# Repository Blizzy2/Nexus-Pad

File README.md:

This is Nexus Pad its a simple macro pad with 6 kays and a cool space design.

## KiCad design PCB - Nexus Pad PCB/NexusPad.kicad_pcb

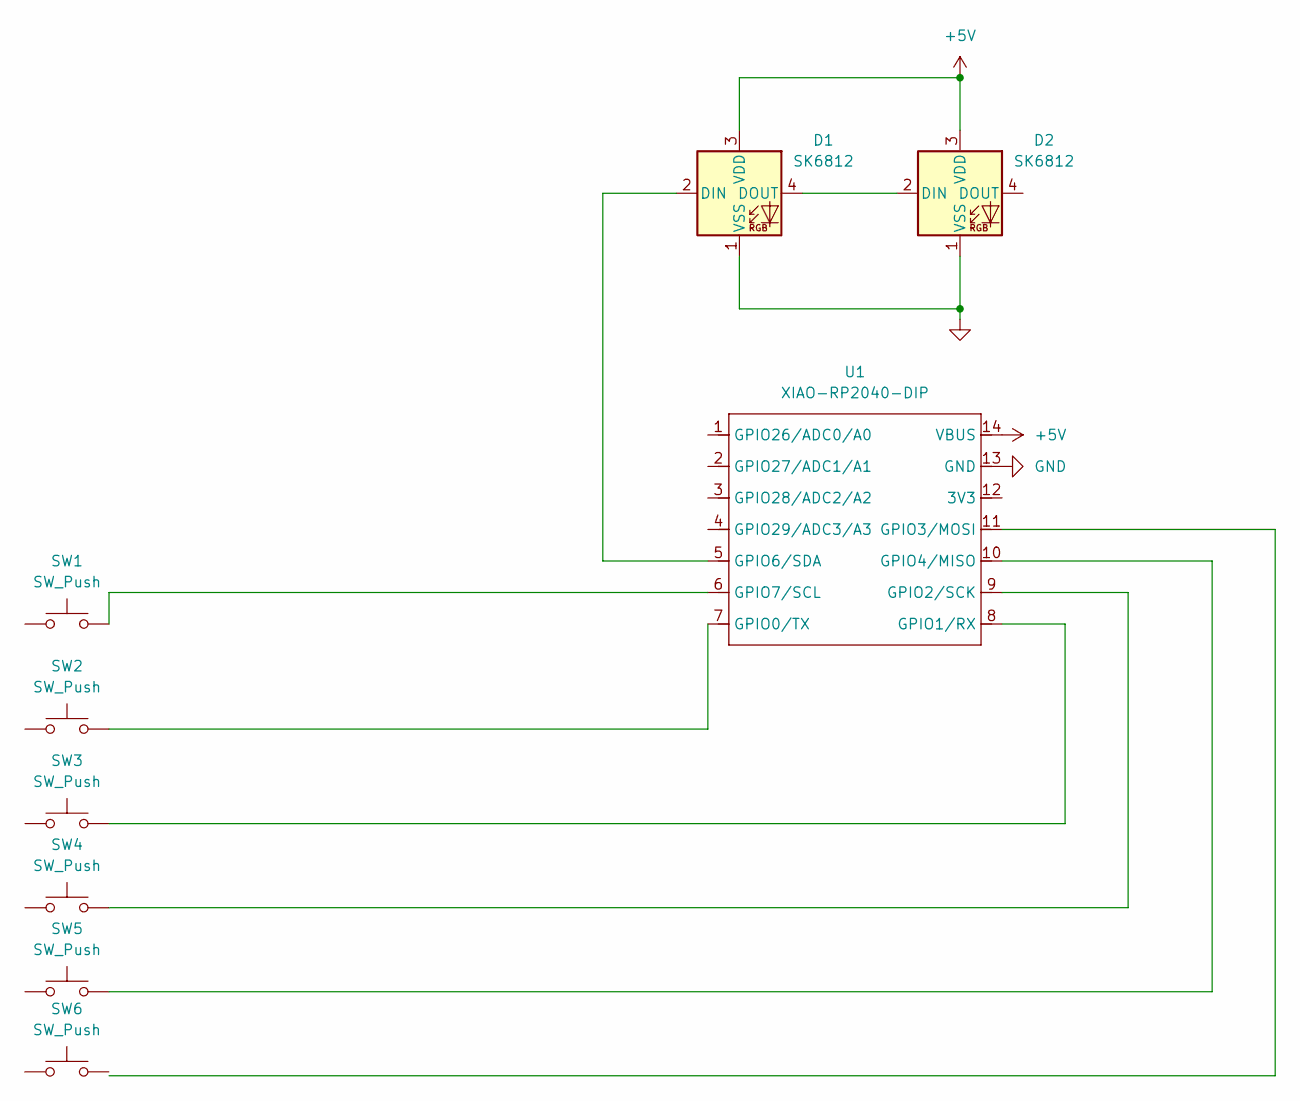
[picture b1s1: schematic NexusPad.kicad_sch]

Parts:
D1, D2: SK6812; LED_SK6812_PLCC4_5.0x5.0mm_P3.2mm
SW1, SW2, SW3, SW4, SW5, SW6: SW_Push; SW_Cherry_MX_1.00u_PCB
U1: XIAO-RP2040-DIP

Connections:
+5V: D1.3 (VDD), D2.3 (VDD), U1.14 (VBUS)
GND: D1.1 (VSS), D2.1 (VSS), U1.13 (GND)
unnamed: D1.2 (DIN), U1.5 (GPIO6/SDA)
unnamed: D1.4 (DOUT), D2.2 (DIN)
unnamed: SW2.2, U1.7 (GPIO0/TX)
unnamed: SW3.2, U1.8 (GPIO1/RX)
unnamed: SW4.2, U1.9 (GPIO2/SCK)
unnamed: SW5.2, U1.10 (GPIO4/MISO)
unnamed: SW1.2, U1.6 (GPIO7/SCL)

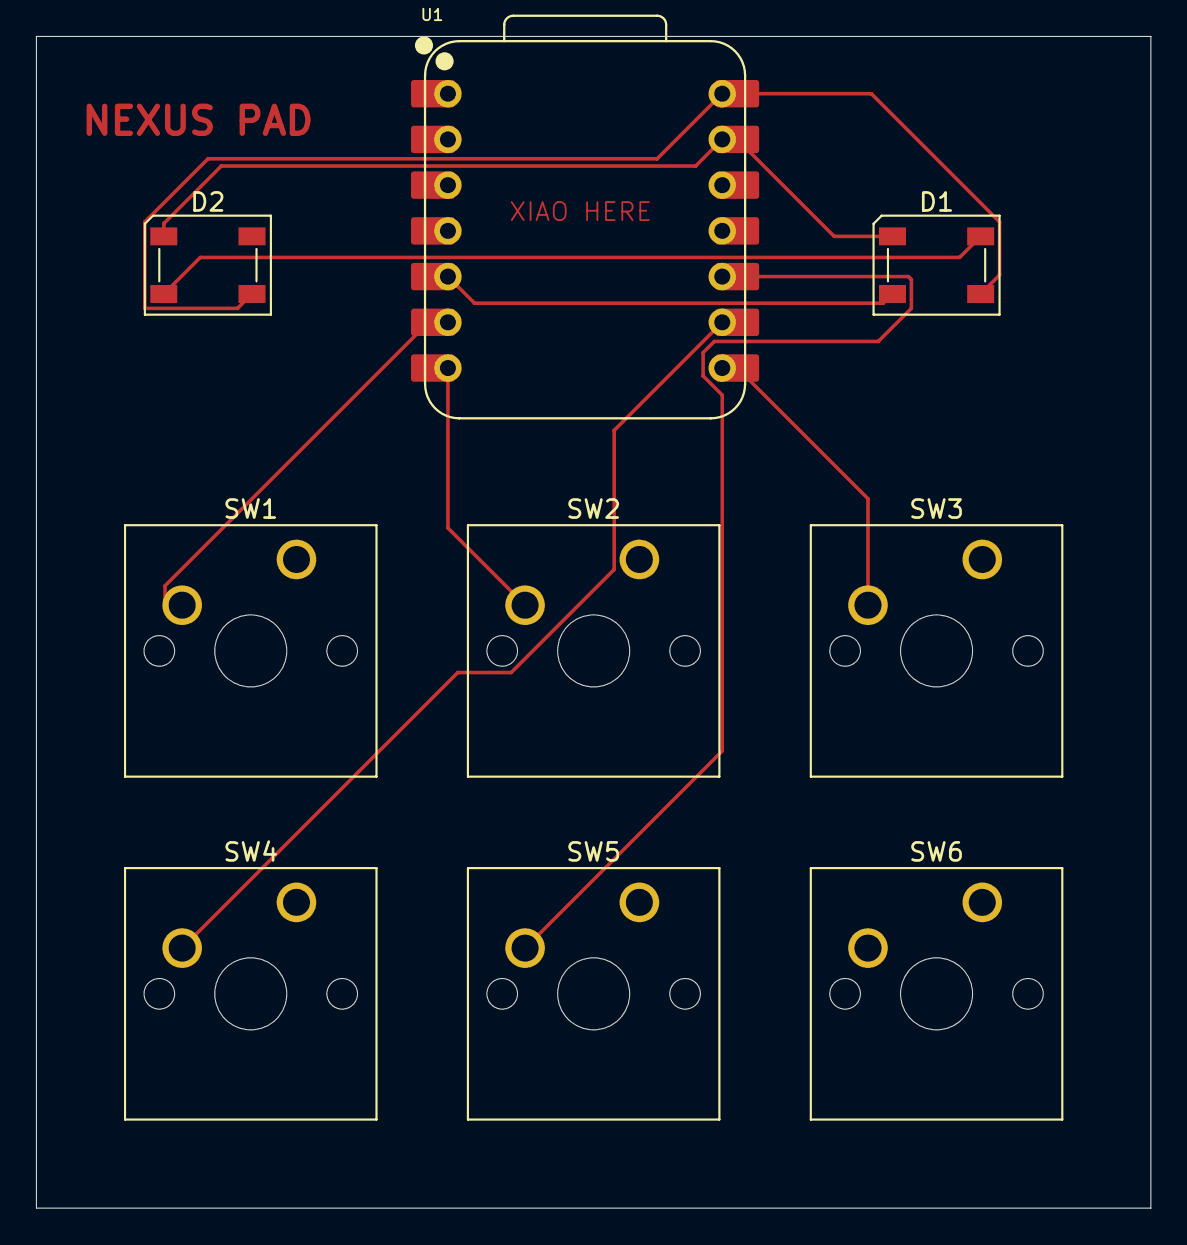
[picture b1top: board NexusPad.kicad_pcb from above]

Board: 2 copper layers, 61.9 x 65.1 mm, 9 parts (0 on the bottom side), 9 nets.

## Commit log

2026-01-31 README
